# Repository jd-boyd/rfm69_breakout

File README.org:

* Retired.

Moved to https://github.com/jd-boyd/bts_ref_dev_adapter/tree/main/rfm69_breakout

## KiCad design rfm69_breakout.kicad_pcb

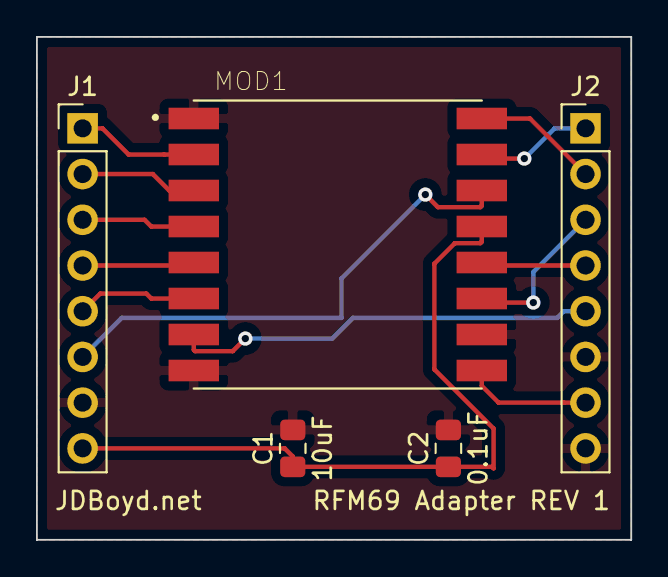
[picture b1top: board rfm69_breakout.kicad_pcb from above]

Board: 2 copper layers, 33.0 x 27.9 mm, 5 parts (0 on the bottom side), 14 nets.

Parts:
C1: 10uF; C_0805_2012Metric_Pad1.15x1.40mm_HandSolder
C2: 0.1uF; C_0805_2012Metric_Pad1.15x1.40mm_HandSolder
J1, J2: Conn_01x08; PinHeader_1x08_P2.54mm_Vertical
MOD1: RFM98W-433S2; XCVR_RFM98W-433S2

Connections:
+3V3: C1.1, C2.1, J1.8, MOD1.13
ANT: J2.7, MOD1.9
DIO0: J1.6, MOD1.14
DIO1: J2.1, MOD1.15
DIO2: J2.2, MOD1.16
DIO3: J2.3, MOD1.11
DIO4: J2.4, MOD1.12
DIO5: J2.5, MOD1.7
GND: C1.2, C2.2, J1.7, J2.6, J2.8, MOD1.1, MOD1.8, MOD1.10
MISO: J1.1, MOD1.2
MOSI: J1.2, MOD1.3
NSS: J1.4, MOD1.5
RESET: J1.5, MOD1.6
SCK: J1.3, MOD1.4

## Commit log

2020-03-03 Import original snapeda part.
2020-03-03 Alter snapeda part to remove x_1 pins.
2020-03-03 Import .gitignore for kicad projects.
2020-03-03 Rev 1 files.
2023-09-11 Add retired notice.
